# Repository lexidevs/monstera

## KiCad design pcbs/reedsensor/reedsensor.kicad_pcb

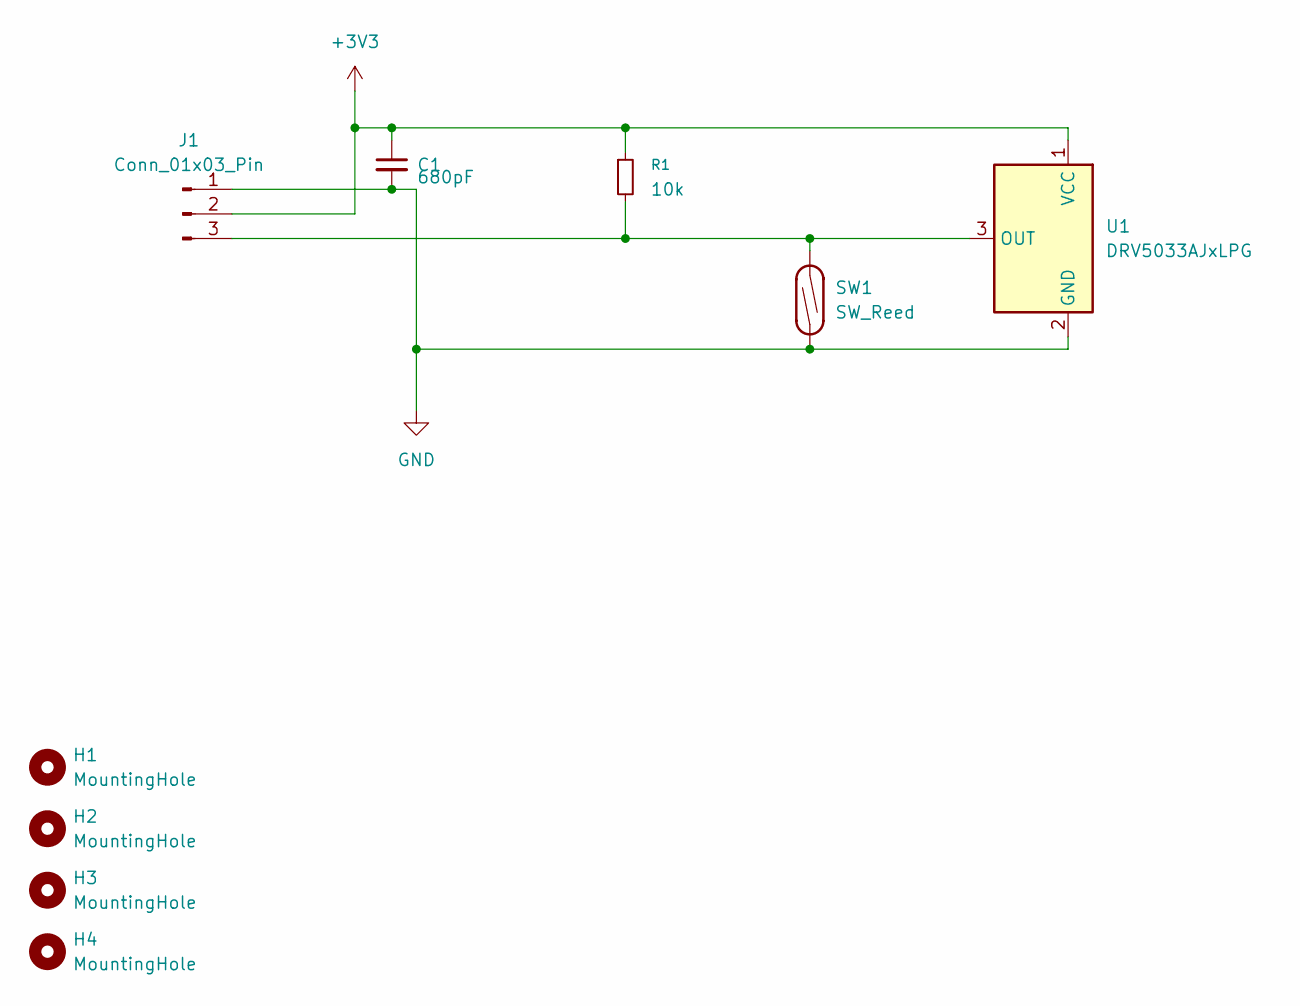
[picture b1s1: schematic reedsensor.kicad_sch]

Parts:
C1: 680pF; C_0805_2012Metric_Pad1.18x1.45mm_HandSolder
H1, H2, H3, H4: MountingHole; MountingHole_2.2mm_M2
J1: Conn_01x03_Pin; JST_PH_S3B-PH-K_1x03_P2.00mm_Horizontal
R1: 10k; R_0805_2012Metric_Pad1.20x1.40mm_HandSolder
SW1: SW_Reed; SW_SPST_REED_CT05-XXXX-J1
U1: DRV5033AJxLPG; TO-92_Inline

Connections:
+3V3: C1.1, J1.2, R1.1, U1.1 (VCC)
GND: C1.2, J1.1, SW1.1, U1.2 (GND)
unnamed: J1.3, R1.2, SW1.2, U1.3 (OUT)

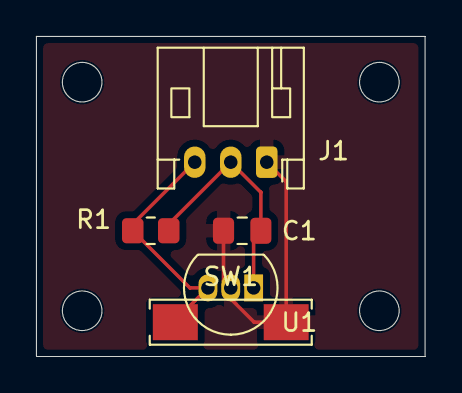
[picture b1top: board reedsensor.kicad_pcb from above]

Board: 2 copper layers, 21.6 x 17.8 mm, 9 parts (0 on the bottom side), 3 nets.

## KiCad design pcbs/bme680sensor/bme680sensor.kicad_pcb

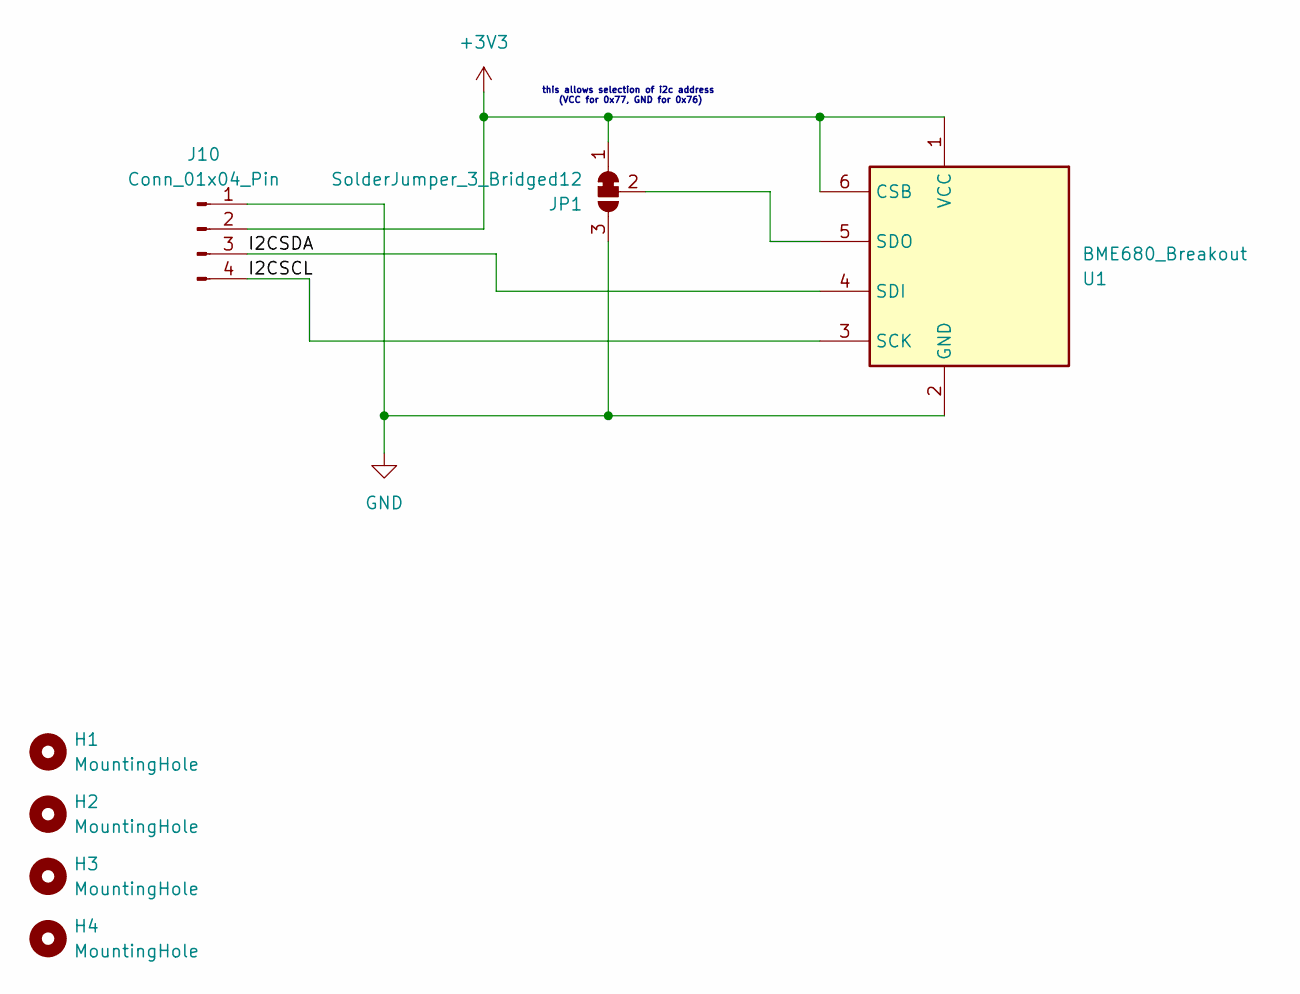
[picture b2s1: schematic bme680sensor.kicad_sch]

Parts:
H1, H2, H3, H4: MountingHole
J10: Conn_01x04_Pin; JST_PH_S4B-PH-K_1x04_P2.00mm_Horizontal
JP1: SolderJumper_3_Bridged12; SolderJumper-3_P1.3mm_Bridged12_RoundedPad1.0x1.5mm
U1: BME680_Breakout; BME680_Breakout_Board

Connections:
+3V3: J10.2, JP1.1 (A), U1.1 (VCC), U1.6 (CSB)
/I2CSCL: J10.4, U1.3 (SCK)
/I2CSDA: J10.3, U1.4 (SDI)
GND: J10.1, JP1.3 (B), U1.2 (GND)
unnamed: JP1.2 (C), U1.5 (SDO)

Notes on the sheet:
this allows selection of i2c address (VCC for 0x77, GND for 0x76)

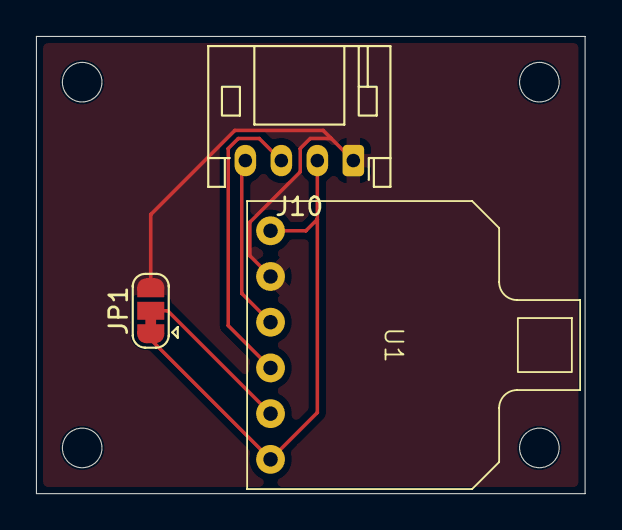
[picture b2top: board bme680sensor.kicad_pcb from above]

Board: 2 copper layers, 30.5 x 25.4 mm, 7 parts (0 on the bottom side), 5 nets.

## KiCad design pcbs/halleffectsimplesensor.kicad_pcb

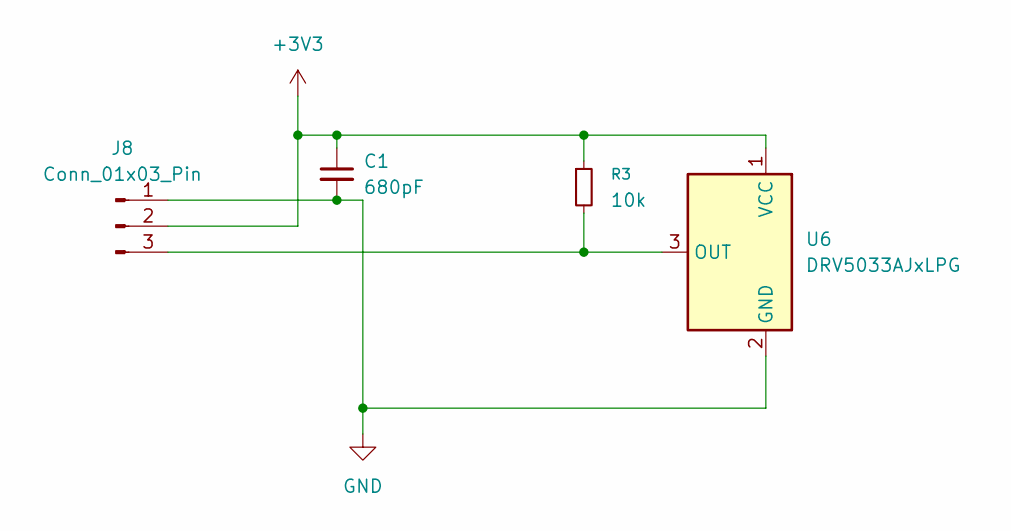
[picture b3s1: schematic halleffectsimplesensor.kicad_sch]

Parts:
C1: 680pF
J8: Conn_01x03_Pin
R3: 10k
U6: DRV5033AJxLPG; TO-92_Inline

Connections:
+3V3: C1.1, J8.2, R3.1, U6.1 (VCC)
GND: C1.2, J8.1, U6.2 (GND)
unnamed: J8.3, R3.2, U6.3 (OUT)

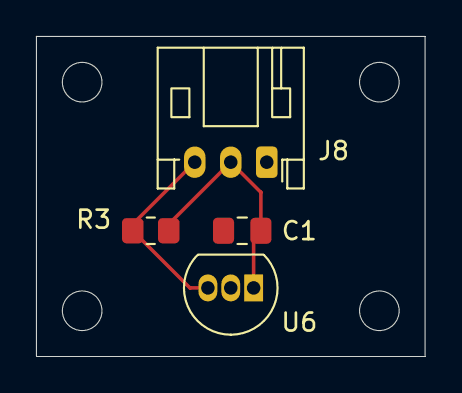
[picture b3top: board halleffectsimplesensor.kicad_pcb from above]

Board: 2 copper layers, 21.6 x 17.8 mm, 8 parts (0 on the bottom side), 3 nets.

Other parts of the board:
H1, H2, H3, H4: MountingHole_2.2mm_M2

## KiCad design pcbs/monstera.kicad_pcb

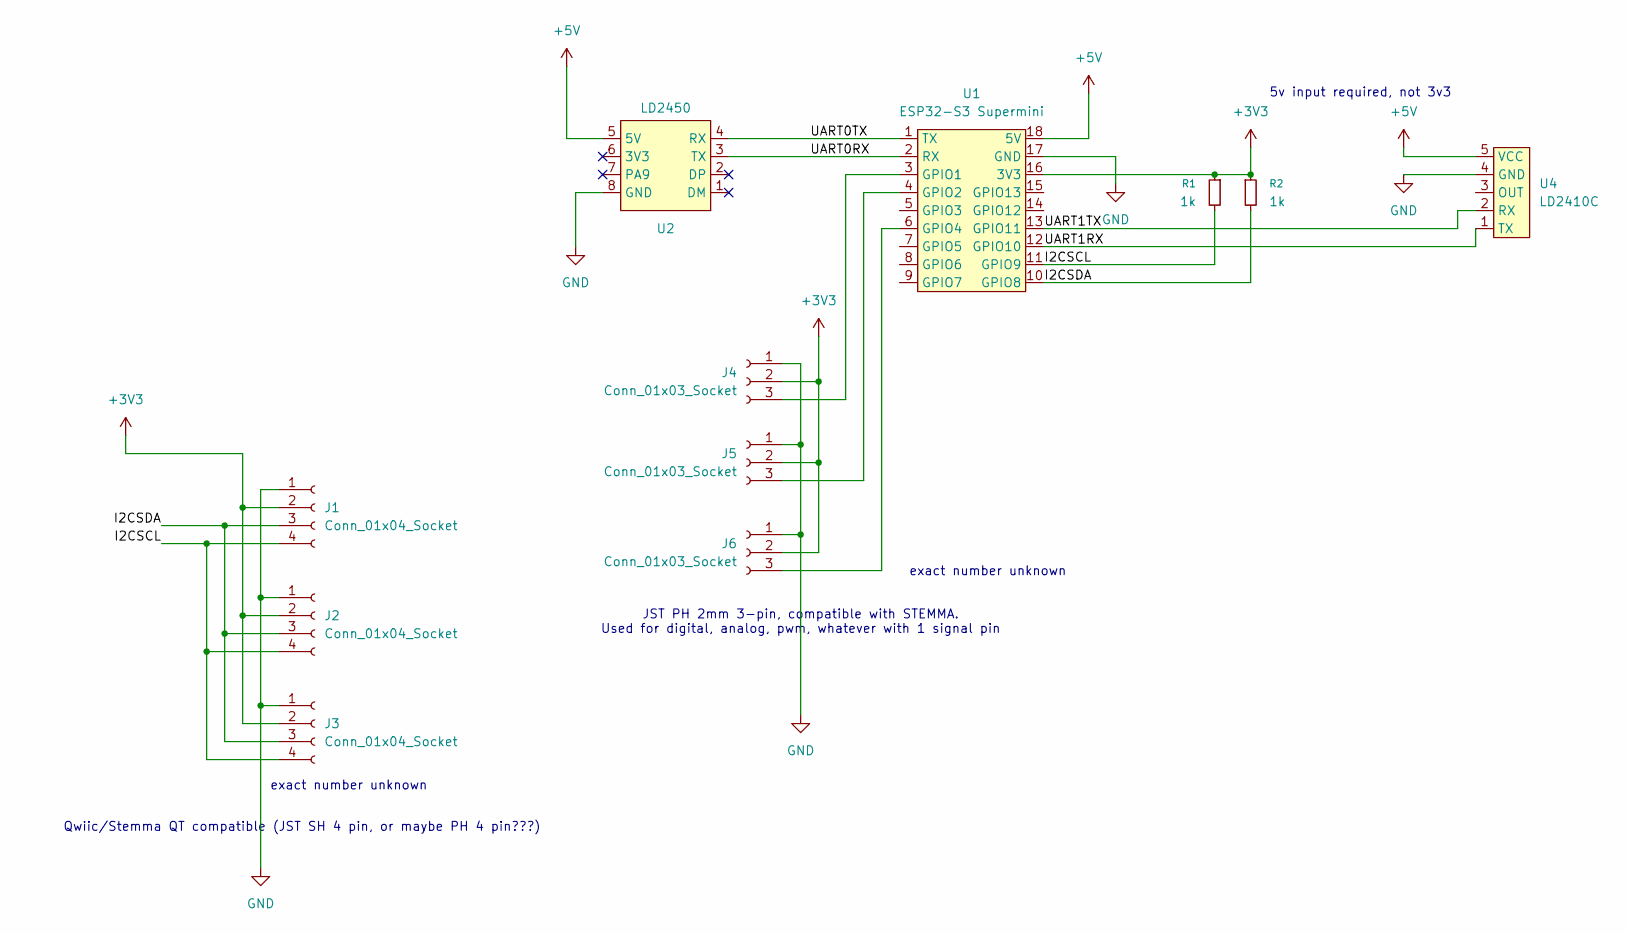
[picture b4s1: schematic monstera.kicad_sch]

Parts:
J1, J2, J3: Conn_01x04_Socket; JST_PH_S4B-PH-K_1x04_P2.00mm_Horizontal
J4, J5, J6: Conn_01x03_Socket; JST_PH_S3B-PH-K_1x03_P2.00mm_Horizontal
R1, R2: 1k; R_0805_2012Metric_Pad1.20x1.40mm_HandSolder
U1: ESP32-S3 Supermini
U2: LD2450; ld2450
U4: LD2410C; ld2410c

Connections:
+3V3: J1.2, J2.2, J3.2, J4.2, J5.2, J6.2, R1.1, R2.1, U1.16 (3V3)
+5V: U1.18 (5V), U2.5 (5V), U4.5 (VCC)
/I2CSCL: J1.4, J2.4, J3.4, R1.2, U1.11 (GPIO9)
/I2CSDA: J1.3, J2.3, J3.3, R2.2, U1.10 (GPIO8)
/UART0RX: U1.2 (RX), U2.3 (TX)
/UART0TX: U1.1 (TX), U2.4 (RX)
/UART1RX: U1.12 (GPIO10), U4.1 (TX)
/UART1TX: U1.13 (GPIO11), U4.2 (RX)
GND: J1.1, J2.1, J3.1, J4.1, J5.1, J6.1, U1.17 (GND), U2.8 (GND), U4.4 (GND)
unnamed: J4.3, U1.3 (GPIO1)
unnamed: J5.3, U1.4 (GPIO2)
unnamed: J6.3, U1.6 (GPIO4)

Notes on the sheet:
5v input required, not 3v3
Qwiic/Stemma QT compatible (JST SH 4 pin, or maybe PH 4 pin???)
exact number unknown
JST PH 2mm 3-pin, compatible with STEMMA. Used for digital, analog, pwm, whatever with 1 signal pin

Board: 2 copper layers, 11 parts (0 on the bottom side), 12 nets, no tracks yet.

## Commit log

2026-04-13 brainstorming of initial concepts
2026-04-13 Initialize kicad 10.0 project
2026-04-13 Add custom symbol library, and make symbols for esp32-s3 supermini and ld2410c
2026-04-13 Update PCBs to include i2c connector
2026-04-13 Basic case layout (subject to change), connector
2026-04-13 CAD: Seperate connector, beginnings of assembly!
2026-04-14 kicad: Add i2c hall effect sensor
2026-04-14 kicad: add simple hall effect, reed, and bme680 sensors
2026-04-14 add ld2450, recreate simple hall effect sensor, add ssd1306 display
2026-04-14 try to fix kicad weirdness
2026-04-14 create aloe repo and submodule for easier library reuse
2026-04-16 Initial PCB layout
2026-04-16 pcb: remove OLED display
2026-04-17 make sensor pcbs
2026-04-17 subdirectories for the different boards, to keep the directory from being a mess
2026-04-17 reed and hall effect sensor, test gerber files (not ready for production)
2026-04-17 Create IOboard schematic, and begin generic i2c board
